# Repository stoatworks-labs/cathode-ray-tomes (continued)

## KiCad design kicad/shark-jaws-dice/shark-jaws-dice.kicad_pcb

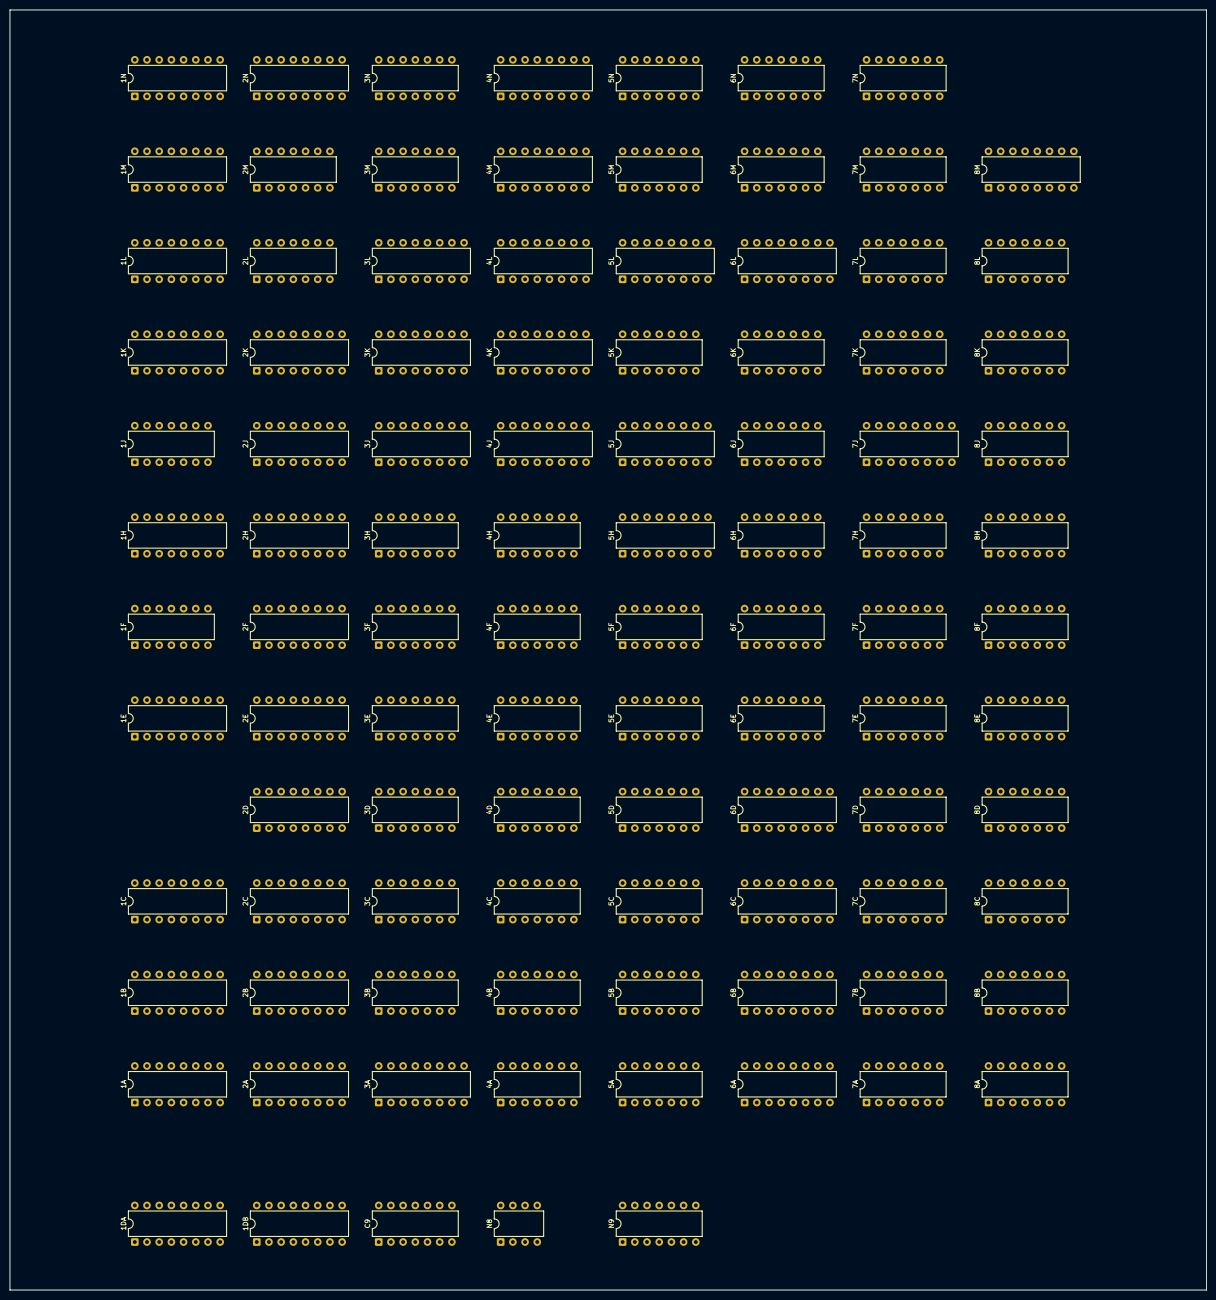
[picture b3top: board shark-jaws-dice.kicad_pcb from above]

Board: 2 copper layers, 249.2 x 266.6 mm, 99 parts (0 on the bottom side), 315 nets, no tracks yet.

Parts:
1A, 1B, 1H, 1K, 3A, 6D: 9322; DIP-16_W7.62mm
1C, 3L, 8M: 9314; DIP-16_W7.62mm
1DA, 1DB: 74S287; DIP-16_W7.62mm
1E: 74174; DIP-16_W7.62mm
1F, 7L: 7486; DIP-14_W7.62mm
1J, 5B: 7430; DIP-14_W7.62mm
1L, 1M, 1N, 2J, 2K, 2N, 4J, 4K, 4M, 4N, 5H, 5J: 9316; DIP-16_W7.62mm
2A, 2B, 2C, 2D, 2E, 2F, 2H: 74165; DIP-16_W7.62mm
2L, 4B, 8B, 8F, 8J: 7404; DIP-14_W7.62mm
2M, 4A, 5K, 7N, 8K: 7400; DIP-14_W7.62mm
3B: 74164; DIP-14_W7.62mm
3C, 3E, 5M, 5N, 7E, 8A, 8L: 7402; DIP-14_W7.62mm
3D, 3M, 7D, 7H: 7408; DIP-14_W7.62mm
3F, 4E, 5A, 6H, 6M, 6N, 7C, 7F, 7K, 7M, 8C, 8D, 8E: 7474; DIP-14_W7.62mm
3H, 4C: 7420; DIP-14_W7.62mm
3J, 3K, 4L: 7485; DIP-16_W7.62mm
3N, 4D, 6K: 74107; DIP-14_W7.62mm
4F, 6J, 7B, 8H: 7410; DIP-14_W7.62mm
4H: 7427; DIP-14_W7.62mm
5C, 5D, 5E, 5F, 7A: 7493; DIP-14_W7.62mm
5L, 6L: 74153; DIP-16_W7.62mm
6A, 6B: 9312; DIP-16_W7.62mm
6C: 7448; DIP-16_W7.62mm
6E, 6F: 7490; DIP-14_W7.62mm
7J: 9310; DIP-16_W7.62mm
C9: 556; DIP-14_W7.62mm
N8: 555; DIP-8_W7.62mm
N9: 556; DIP-14_W7.62mm

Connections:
1A-1: 1A.1, 1B.1, 3A.1, 6L.9
1A-4: 1A.4, 2D.6, 2E.6, 2F.6, 2H.6
1A-7: 1A.7, 2D.5, 2E.5, 2F.5, 2H.5
1A-9: 1A.9, 2D.3, 2E.3, 2F.3, 2H.3
1A-12: 1A.12, 2D.4, 2E.4, 2F.4, 2H.4
1B-4: 1B.4, 2D.14, 2E.14, 2F.14, 2H.14
1B-7: 1B.7, 2D.13, 2E.13, 2F.13, 2H.13
1B-9: 1B.9, 2D.11, 2E.11, 2F.11, 2H.11
1B-12: 1B.12, 2D.12, 2E.12, 2F.12, 2H.12
1C-1: 1C.1, 4A.8
1DA-1: 1DA.1, 1DB.1
1DA-2: 1DA.2, 1DB.2
1DA-5: 1DA.5, 1DB.5
1DA-13: 1DA.13, 3E.1
1DB-15: 1DB.15, N9.9
1E-13: 1E.13, 1F.11
1E-14: 1E.14, 7E.10
1F-4: 1F.4, 1H.12
1F-5: 1F.5, 1F.10, 4H.6
1F-9: 1F.9, 1H.7
1F-12: 1F.12, 3D.3
1F-13: 1F.13, 7K.5
1H-3: 1H.3, 1K.4
1H-6: 1H.6, 1K.7
1H-10: 1H.10, 1K.9
1H-13: 1H.13, 1K.12
1J-3: 1J.3, 2L.10
1J-4: 1J.4, 2L.8
1J-8: 1J.8, 6H.10
1L-3: 1L.3, 8L.2, 8M.13
1L-4: 1L.4, 7L.6
1L-9: 1L.9, 1M.9, 2M.6
1L-11: 1L.11, 3M.9
1L-15: 1L.15, 1M.7, 2M.5
1M-15: 1M.15, 2M.4, 3M.10
1N-7: 1N.7, 2M.1, 2N.15
1N-9: 1N.9, 2M.3, 2N.9
2A-1: 2A.1, 3A.4, 7N.9
2A-3: 2A.3, 2B.3, 2C.3
2A-4: 2A.4, 2B.4, 2C.4
2A-5: 2A.5, 2B.5, 2C.5
2A-6: 2A.6, 2B.6, 2C.6
2A-9: 2A.9, 2B.10
2A-11: 2A.11, 2B.11, 2C.11
2A-12: 2A.12, 2B.12, 2C.12
2A-13: 2A.13, 2B.13, 2C.13
2A-14: 2A.14, 2B.14, 2C.14
2A-15: 2A.15, 2B.15, 2C.15, 3C.8, 7K.8
2B-9: 2B.9, 2C.10
2C-1: 2C.1, 3A.7, 7N.10
2C-7: 2C.7, 3C.9
2D-1: 2D.1, 3B.13
2D-7: 2D.7, 3C.12
2D-15: 2D.15, 3C.11, 3H.8
2E-1: 2E.1, 3A.9
2E-2: 2E.2, 2F.2, 2H.2, 3F.5
2E-7: 2E.7, 3E.9
2E-10: 2E.10, 2F.9
2E-15: 2E.15, 2F.15, 2H.15, 3E.8, 3F.8
2F-10: 2F.10, 2H.9
2H-1: 2H.1, 3A.12
2J-7: 2J.7, 2K.15, 3M.5
2J-9: 2J.9, 2K.9, 2M.8
2J-15: 2J.15, 3M.4
2K-3: 2K.3, 2L.4, 2M.13
2K-4: 2K.4, 2M.11
2L-3: 2L.3, 3L.12
2L-5: 2L.5, 3H.6
2L-6: 2L.6, 3M.13
2L-12: 2L.12, 3H.5
2M-10: 2M.10, 3M.6, 3N.9
2M-12: 2M.12, 3L.10
2N-4: 2N.4, 8L.4
3C-1: 3C.1, 3D.13
3C-4: 3C.4, 3D.10
3D-2: 3D.2, 3E.4
3F-2: 3F.2, 3F.6
3F-4: 3F.4, 3F.9
3J-2: 3J.2, 3K.7
3J-3: 3J.3, 3K.6
3J-7: 3J.7, 3L.7
3L-1: 3L.1, 5K.6
3L-3: 3L.3, 4L.7
3L-15: 3L.15, 5N.2, 8J.13
3M-1: 3M.1, 8K.3
3M-2: 3M.2, 8J.9, 8K.6
3M-3: 3M.3, 5H.4
3N-12: 3N.12, 4F.4, 4M.15
4A-3: 4A.3, 4A.4, 7L.10
4A-5: 4A.5, 4B.10
4A-11: 4A.11, 7D.5
4A-12: 4A.12, 4H.8
4A-13: 4A.13, 4B.12
4B-9: 4B.9, C9.9
4C-6: 4C.6, 7C.13
4C-8: 4C.8, 7D.4
4E-3: 4E.3, 8F.12
4E-5: 4E.5, 5A.11, 5D.14
4E-12: 4E.12, 4F.12
4F-3: 4F.3, 4M.7, 4N.15
4F-6: 4F.6, 4M.9, 4N.9
4F-8: 4F.8, 7E.5
4F-9: 4F.9, 7E.1
4H-3: 4H.3, 6K.3
4H-4: 4H.4, 8J.6
4H-12: 4H.12, 4J.4
4J-3: 4J.3, 6J.6
4J-9: 4J.9, 4K.9, 5K.8
4J-15: 4J.15, 4K.7, 5K.10
4N-3: 4N.3, 5N.3, 5N.4
4N-4: 4N.4, 5N.1
5A-12: 5A.12, 5B.8
5H-5: 5H.5, 8J.8
5H-9: 5H.9, 5J.9, 5K.11
5H-15: 5H.15, 5J.10
5J-15: 5J.15, 5K.13, 6K.9
5K-3: 5K.3, 5L.1
5N-6: 5N.6, 6N.5
6A-1: 6A.1, 6C.15
6A-4: 6A.4, 6C.12
6A-5: 6A.5, 6C.9
6A-9: 6A.9, 6C.11
6A-15: 6A.15, 7E.9
6B-1: 6B.1, 6C.13
6B-4: 6B.4, 6C.14
6B-9: 6B.9, 6C.10
6B-15: 6B.15, 7E.8
6C-1: 6C.1, 6D.7
6C-2: 6C.2, 6D.12
6C-6: 6C.6, 6D.9
6C-7: 6C.7, 6D.4
6D-2: 6D.2, 6F.1, 6F.12
6D-3: 6D.3, 6E.1, 6E.12
6D-5: 6D.5, 6F.9
6D-6: 6D.6, 6E.9
6D-10: 6D.10, 6E.11
6D-11: 6D.11, 6E.14, 6F.11
6D-13: 6D.13, 6E.8
6D-14: 6D.14, 6F.8
6F-14: 6F.14, 7D.3
6H-2: 6H.2, 7J.11, 8L.8
6H-5: 6H.5, 6J.10
6J-2: 6J.2, 7H.6, 8H.3
6J-3: 6J.3, 7L.11
6J-8: 6J.8, 7J.1
6J-12: 6J.12, 7H.2
6L-7: 6L.7, 7K.3
6L-10: 6L.10, 6M.6
6L-11: 6L.11, 6M.9
6N-1: 6N.1, 7N.6
6N-8: 6N.8, 6N.12
7A-1: 7A.1, 7A.12
7A-11: 7A.11, 8A.12
7B-4: 7B.4, 7B.5
7B-6: 7B.6, 8E.2
7B-12: 7B.12, 7C.1
7C-3: 7C.3, 7D.11
7D-6: 7D.6, 7E.6
7E-11: 7E.11, 8C.1, 8C.12, 8C.13
7E-13: 7E.13, 8E.4
7F-1: 7F.1, 7H.3
7F-13: 7F.13, 7H.11
7H-1: 7H.1, 8H.6
7H-8: 7H.8, 8H.10, 8H.13
7H-12: 7H.12, 8H.12
7H-13: 7H.13, 8H.8
7J-7: 7J.7, 8J.4
7J-12: 7J.12, 8L.9
7J-15: 7J.15, 8J.3
7L-1: 7L.1, 8M.15
7L-2: 7L.2, 7M.5
7L-3: 7L.3, 8J.1, 8L.5
7L-4: 7L.4, 8L.1
7L-5: 7L.5, 7M.9
7L-8: 7L.8, 8L.11, 8L.12
7M-3: 7M.3, 7N.3
7M-11: 7M.11, 7N.11
7N-4: 7N.4, 7N.5, N8.3
8A-9: 8A.9, 8A.13
8A-10: 8A.10, 8A.11
8C-2: 8C.2, 8C.9
8C-6: 8C.6, 8D.1, 8D.13
8D-5: 8D.5, 8D.12
8E-11: 8E.11, 8F.10
8F-6: 8F.6, 8H.9
8K-11: 8K.11, C9.6
8L-3: 8L.3, 8M.12
+5V: 1A.16, 1B.16, 1E.16, 1F.14, 1H.16, 1J.14, 1K.16, 1L.16, 1M.16, 1N.16, 2A.16, 2B.16, 2C.16, 2D.16, 2E.16, 2F.16, 2H.16, 2J.16, 2K.16, 2L.14, 2M.14, 2N.16, 3A.16, 3B.14, 3C.14, 3D.14, 3E.14, 3F.14, 3H.14, 3J.16, 3K.16, 3M.14, 3N.14, 4A.14, 4B.14, 4C.14, 4D.14, 4E.14, 4F.14, 4H.14, 4J.16, 4K.16, 4L.16, 4M.16, 4N.16, 5A.14, 5B.14, 5C.5, 5D.5, 5E.5, 5F.5, 5H.16, 5J.16, 5K.14, 5L.16, 5M.14, 5N.14, 6A.16, 6B.16, 6C.16, 6D.16, 6E.5, 6F.5, 6H.14, 6J.14, 6K.14, 6L.16, 6M.14, 6N.14, 7A.5, 7B.14, 7C.14, 7D.14, 7E.14, 7F.14, 7H.14, 7J.16, 7K.14, 7L.14, 7M.14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
GND: 1A.8, 1A.15, 1B.8, 1B.15, 1C.2, 1C.5, 1C.11, 1C.14, 1E.8, 1F.7, 1H.8, 1H.15, 1J.7, 1K.8, 1K.15, 1L.8, 1M.6, 1M.8, 1N.4, 1N.5, 1N.6, 1N.8, 2A.8, 2A.10, 2B.8, 2C.8, 2D.8, 2D.10, 2E.8, 2F.8, 2H.8, 2H.10, 2J.8, 2K.5, 2K.8, 2L.7, 2M.7, 2N.8, 3A.8, 3A.15, 3B.7, 3C.7, 3D.7, 3E.7, 3F.7, 3H.7, 3J.8, 3K.8, 3L.2, 3L.5, 3L.11, 3L.14, 3M.7, 3N.7, 4A.7, 4B.7, 4C.7, 4D.7, 4E.7, 4F.7, 4H.7, 4J.8, 4K.4, 4K.5, 4K.6, 4K.8, 4L.8, 4M.5, 4M.6, 4M.8, 4N.5, 4N.8, 5A.7, 5B.7, 5C.10, 5D.10, 5E.10, 5F.10, 5H.3, 5H.8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
VCC: 1C.9, 1E.1, 1L.1, 1L.5, 1L.6, 1L.7, 1M.1, 1M.3, 1M.4, 1M.5, 1M.10, 1N.1, 1N.3, 1N.10, 2J.1, 2J.3, 2J.4, 2J.5, 2J.6, 2J.10, 2K.1, 2K.6, 2K.7, 2K.10, 2N.1, 2N.5, 2N.6, 2N.7, 2N.10, 3B.1, 3B.2, 3F.1, 3F.10, 3J.4, 3K.2, 3K.3, 3K.4, 3K.9, 3K.10, 3K.11, 3K.12, 3L.9, 3N.1, 3N.4, 3N.8, 3N.10, 3N.11, 3N.13, 4D.1, 4D.4, 4D.8, 4D.11, 4E.1, 4E.4, 4E.10, 4E.13, 4J.1, 4J.5, 4J.6, 4J.7, 4J.10, 4K.3, 4K.10, 4L.3, 4L.4, 4M.1, 4M.3, 4M.4, 4M.10, 4N.1, 4N.6, 4N.7, 4N.10, 5A.2, 5A.4, 5A.10, 5A.13, 5B.1, 5B.2, 5B.12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
_1H: 4B.3, 4J.2, 4K.2, 5D.1, 5D.12, 8M.4
_1Hn: 1E.9, 1N.2, 2N.2, 4B.4
_1V: 4F.1, 5F.1, 5F.12
_2H: 4A.10, 5B.4, 5D.9, 6A.11, 8M.6
_2V: 5F.9, 6B.11
_4H: 1E.6, 4B.1, 5B.5, 5D.8, 6A.12
_4Hn: 3B.8, 4A.9, 4B.2
_4V: 4B.11, 4F.2, 5F.8, 6B.12
_8H: 1E.4, 3E.6, 5C.14, 5D.11, 6A.10, 6B.10
_8V: 5E.14, 5F.11, 6A.13, 6B.13
_16H: 1E.3, 3E.5, 4B.13, 4C.13, 5A.3, 5C.1, 5C.12, 7D.13
_16V: 4C.2, 4F.11, 5E.1, 5E.12
_32H: 4C.9, 4H.11, 5C.9, 7B.2
_32V: 4C.1, 4F.10, 5E.9, 7C.11
_64H: 4C.10, 4H.10, 5B.6, 5C.8, 7D.12
_64V: 4C.4, 5E.8, 7E.3, 8C.3, 8C.11
_128H: 4C.12, 4D.12, 4H.9, 5B.3, 5C.11, 7B.1
_128V: 4C.5, 4D.9, 5E.11, 7E.2, 8F.5, 8H.2
_256H: 4D.3, 5B.11, 7B.13, 8H.5
_256Hn: 4D.2, 6D.1, 6J.13
_256V: 4D.5, 4F.13, 6K.12, 8E.3
_AH3: 1J.1, 4J.12
_AH4: 2L.9, 4J.11
_AHWIN: 4K.15, 5K.9, 7K.11
_ATTRACT: 7B.3, 8D.3, 8D.11, 8E.9
_ATTRACTn: 6M.2, 7D.1, 7F.2, 7F.12, 8E.8
_AV1: 1H.11, 1J.6, 5H.14
_AV2: 1H.14, 1J.2, 5H.13
_AV3: 1H.5, 1J.5, 5H.12
_AV4: 1H.2, 2L.11, 3K.13, 5H.11
_AVWIN: 5L.7, 7K.12
_BV1: 1K.11, 2K.14
_BV2: 1K.14, 2K.13
_BV3: 1K.5, 2K.12
_BV4: 1K.2, 2K.11, 3K.14
_BV5: 3D.1, 4N.12
_CATCH: 6H.12, 8J.5, 8L.10
_CH3: 2N.12, 3H.13
_CH4: 2N.11, 3H.12
_CHWIN: 1N.15, 2M.2, 3H.10
_CLOCKn: 2A.2, 2B.2, 2C.2, 2D.2, 3F.3, 4E.2, 4E.6, 4M.2, 4N.2, 8M.3
_COMPBLANK: 1J.12, 8K.8
_CREDITn: 7E.12, 8D.9
_CV1: 1K.10, 1L.10, 6N.9
_CV2: 1K.13, 1L.14
_CV3: 1K.6, 1L.13
_CV4: 1K.3, 1L.12
_CVWIN: 3E.3, 3H.9, 3M.8
_D1: 1A.3, 1B.11, 1C.3, 1DA.12
_D2: 1A.6, 1B.14, 1C.4, 1DA.11
_D3: 1A.13, 1B.5, 1C.6, 1DA.10
_D4: 1A.10, 1B.2, 1C.7, 1DA.9
_D5: 1A.11, 1B.3, 1C.15
_D6: 1A.14, 1B.6, 1C.13
_D7: 1A.5, 1B.13, 1C.12
_D8: 1A.2, 1B.10, 1C.10
_DIVERENABLEn: 1DB.14, 5N.10
_ENDGAMEn: 8F.11, N9.5
_FISHSCORE: 3C.2, 7D.2, C9.5
_HALFSEC: 6H.3, 6H.11, 6M.11, 7A.14, 7J.2, 7K.1, 7M.1, 7M.13, 8B.8, 8M.1
_HALFSECn: 4B.8, 5K.4, 8B.9
_HBLANK: 7C.6, 7H.5, 7N.1
_HBLANKn: 3D.4, 7C.5, 8K.9
_HRESET: 4E.11, 5A.8, 5C.2, 5C.3, 5D.2, 5D.3, 5F.14
_HRESETn: 3B.9, 3F.13, 4D.13, 5A.1, 5A.9
_HSYNC: 2J.2, 2K.2, 5A.6, 5H.2, 5J.2, 6N.3, 7L.9
_HSYNC1: 1L.2, 1M.2, 3C.3, 3C.5, 4B.6, 6N.11
_HSYNCn: 4B.5, 5A.5
_JOYDOWN: 8H.1, 8K.1
_JOYLEFT: 6J.1, 7L.13, 8J.11
_JOYRIGHT: 6M.3, 7L.12, 8H.4
_JOYUP: 8H.11, 8K.5
_LD1An: 3A.3, 3A.5, 3B.3
_LD1Bn: 2B.1, 3B.4
_LD1Cn: 1H.1, 3A.2, 3A.6, 3B.5, 4H.5, 6L.14
_LD2An: 3A.11, 3A.13, 3B.10
_LD2Bn: 2F.1, 3B.11
_LD2Cn: 1K.1, 3A.10, 3A.14, 3B.12, 6L.2
_LH1: 4L.9, 4M.13
_LH2: 4L.11, 4M.12
_LH3: 4L.14, 4M.11, 7K.2
_LH4: 3N.3, 4F.5, 4L.1
_LHWIN: 3F.11, 3N.2
_LRGFISH: 3D.5, 3E.10, 6J.11
_LRGFISHDIR: 6M.12, 8J.12
_LV0: 2J.14, 2L.13, 3K.1
_LV1: 2J.13, 3H.4, 3J.9
_LV2: 2J.12, 3H.2, 3J.11
_LV3: 2J.11, 3H.1, 3J.14
_LV4: 2M.9, 3J.1, 3M.12, 3N.5
_LVWIN: 3E.2, 3F.12, 3M.11
_MEDFISH: 1J.11, 3C.10, 3D.9, 6J.9, 7H.4, 7H.10, 8K.12
_MH1: 4K.14, 4L.10
_MH2: 4K.13, 4L.12
_MH3: 4K.12, 4L.13, 7K.13
_MH4: 4K.11, 4L.15
_MV1: 3K.15, 5J.14, 5L.2
_MV2: 3J.10, 5J.13, 5L.14
_MV3: 3J.12, 5J.12, 5K.1
_MV4: 3J.13, 5J.11, 5K.2
_MV5: 3J.15, 5K.12, 6K.5
_Q: 8D.10, 8E.10, 8F.8
_RESET: 3C.6, 6H.9
_RESETn: 4K.1, 5J.1, 6H.8
_SCOREWIN: 6C.4, 7E.4
_SCOREn: 1E.15, 2L.1
_SHARKENABLEn: 1DA.14, 5N.8, 5N.9, 7N.8
_SMLFISH: 3C.13, 3D.12, 7N.2, 7N.13, 8K.13
_SMLFISHDIR: 6L.13, 8J.2
_START: 6E.2, 6E.3, 6F.2, 6F.3, 7A.2, 7A.3, 8A.8, 8E.6
_STARTn: 8E.5, 8E.13, N8.2, N9.6
_STOPH: 4H.13, 7F.6
_STOPHn: 6J.4, 7F.5
_STOPVn: 7F.9, 8K.2, 8K.4
_SWLEFTn: 4H.1, 6M.1, 8J.10
_V1: 1DA.6, 1DB.6, 1H.9
_V2: 1DA.7, 1DB.7, 1F.6
_V3: 1DA.4, 1DB.4, 1F.8
_V4: 1DA.3, 1DB.3, 1H.4
_VAEQB: 3J.6, 3L.6, 6L.3, 6L.4, 6L.5
_VBLANK: 7C.8, 7H.9, 7N.12
_VBLANKn: 7C.9, 8K.10
_VRESET: 4E.8, 5E.2, 5E.3, 5F.2, 5F.3, 5K.5, 5N.5, 6J.5, 6N.2
_VRESETn: 2N.3, 4A.2, 4D.10, 4E.9, 4H.2, 7F.3, 7F.11, 8L.6
_VSYNCn: 4A.1, 4A.6

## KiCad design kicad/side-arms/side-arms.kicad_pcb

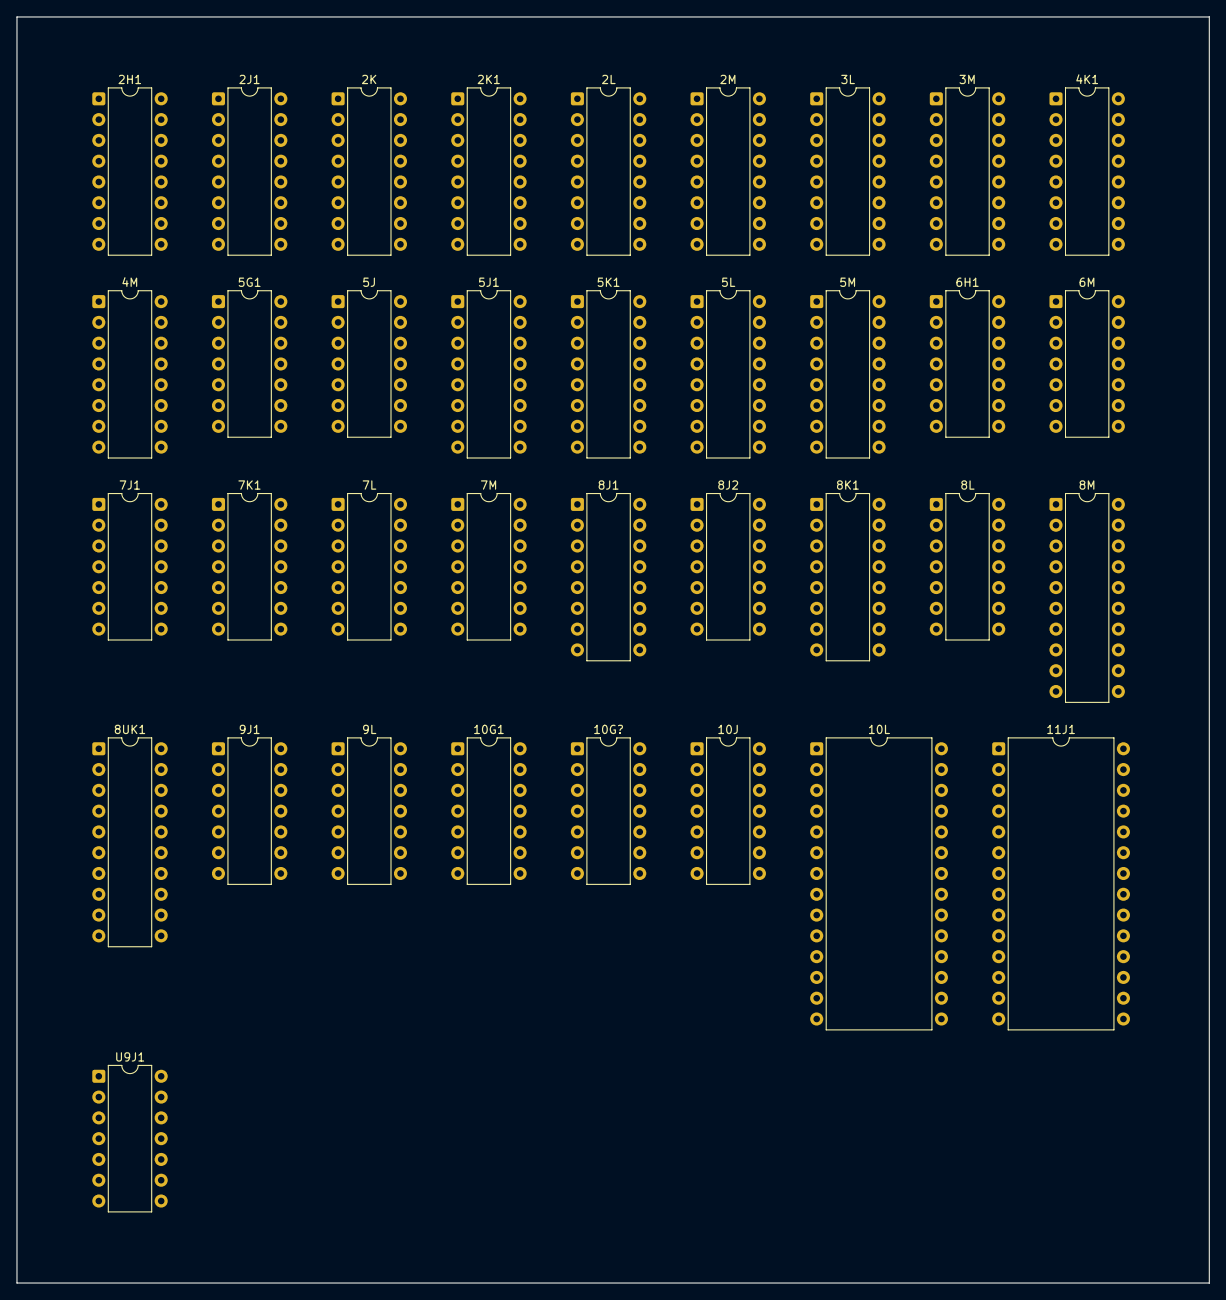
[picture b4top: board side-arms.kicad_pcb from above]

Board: 2 copper layers, 145.7 x 154.7 mm, 36 parts (0 on the bottom side), 149 nets, no tracks yet.

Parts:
2H1, 2J1, 2K, 2K1, 2L, 2M, 5K1, 5M: 74LS283; DIP-16_W7.62mm
3L, 3M, 4K1, 4M, 5J1, 5L, 8J1, 8K1: 74LS191; DIP-16_W7.62mm
5G1, 5J: 74LS08; DIP-14_W7.62mm
6H1, 6M, 8J2, 8L: 74LS30; DIP-14_W7.62mm
7J1, 7L: 74LS74; DIP-14_W7.62mm
7K1, 7M, 10G1, 10G?, 10J: 74LS86; DIP-14_W7.62mm
8M, 8UK1: 74LS374; DIP-20_W7.62mm
9J1, 9L: 74LS00; DIP-14_W7.62mm
10L: 74LS00; DIP-28_W15.24mm
11J1: 27128; DIP-28_W15.24mm
U9J1: 74LS00; DIP-14_W7.62mm

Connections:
/D~U: 4K1.5, 5J1.5, 8J1.5, 8K1.5, 10G1.3
/H6: 2J1.3, 10G1.13
/HS0: 2K1.4, 6H1.12, 10G1.10
/HS1: 2K1.1, 6H1.11, 7K1.13
/HS2: 2K1.13, 6H1.6, 7K1.10, 9J1.2
/HS3: 2K1.10, 6H1.5, 7K1.5
/HS4: 2J1.4, 6H1.4, 7K1.2
/HS5: 2J1.1, 11J1.10
/HS6: 2J1.13, 11J1.9
/HS7: 2J1.10, 11J1.8
/HS8: 10G1.6, 11J1.7
/HSC: 2J1.9, 10G1.5
/HSCAN: 8J1.14, 8K1.14
/O3: 7K1.1, 8UK1.9
/O4: 7K1.4, 8UK1.12
/O5: 7K1.9, 8UK1.15
/O6: 7K1.12, 8UK1.16
/O7: 8UK1.19, 10G1.9
/RCO: 4K1.13, 5J1.4
/Rc: 8J1.4, 8K1.13
/S0: 5K1.4, 11J1.6
/S1: 5K1.1, 9J1.1, 11J1.5
/S2: 5K1.13, 10G1.12, 11J1.4
/S3: 5K1.10, 11J1.3
/S4: 2H1.10, 11J1.25
/S5: 2H1.13, 11J1.24
/S6: 2H1.1, 11J1.21
/S7: 2H1.4, 11J1.23
/STARON: 4K1.11, 5J1.11, 8J1.11, 8K1.11
/VSCAN: 4K1.14, 5J1.14
/sarms/D~U: 3L.5, 3M.5, 4M.5, 5L.5, 10J.3
/sarms/H6: 2L.3, 10J.13
/sarms/HS0: 2M.4, 6M.12, 10J.10
/sarms/HS1: 2M.1, 7M.13
/sarms/HS2: 2M.13, 6M.6, 7M.10
/sarms/HS3: 2M.10, 6M.5, 7M.5
/sarms/HS4: 2L.4, 6M.4, 7M.2
/sarms/HS5: 2L.1, 10L.10
/sarms/HS6: 2L.13, 10L.9
/sarms/HS7: 2L.10, 10L.8
/sarms/HS8: 10J.6, 10L.7
/sarms/HSC: 2L.9, 10J.5
/sarms/HSCAN: 3L.14, 3M.14
/sarms/O0: 8M.19, 10J.9
/sarms/O1: 7M.12, 8M.16
/sarms/O2: 7M.9, 8M.15
/sarms/O3: 7M.4, 8M.12
/sarms/O4: 7M.1, 8M.9
/sarms/RCO: 4M.13, 5L.4
/sarms/Rc: 3L.4, 3M.13
/sarms/S0: 5M.4, 10L.6
/sarms/S1: 5M.1, 10L.5
/sarms/S2: 5M.13, 10J.12, 10L.4
/sarms/S4: 2K.4, 10L.25
/sarms/S5: 2K.1, 10L.24
/sarms/S6: 2K.13, 10L.21
/sarms/S7: 2K.10, 10L.23
/sarms/STARON: 3L.11, 3M.11, 4M.11, 5L.11
/sarms/VSCAN: 4M.14, 5L.14
/sarms/~C4: 2L.7, 2M.9
/sarms/~LD: 7L.1, 8L.4
/~C4: 2J1.7, 2K1.9
/~LD: 7J1.1, 8J2.4
GND: 2K1.7, 2M.7, 3L.1, 3L.9, 3L.10, 3L.15, 3M.1, 3M.4, 3M.9, 3M.10, 3M.15, 4K1.1, 4K1.4, 4K1.9, 4K1.10, 4K1.15, 4M.1, 4M.4, 4M.9, 4M.10, 4M.15, 5J1.1, 5J1.9, 5J1.10, 5J1.15, 5K1.7, 5L.1, 5L.9, 5L.10, 5L.15, 5M.7, 8J1.1, 8J1.9, 8J1.10, 8J1.15, 8K1.1, 8K1.4, 8K1.9, 8K1.10, 8K1.15, 8M.1, 8UK1.1, 10G1.1, 10J.1, 10L.14, 10L.20, 10L.22, 11J1.14, 11J1.20, 11J1.22
unnamed: 2H1.6, 5J1.3
unnamed: 2H1.2, 5J1.2
unnamed: 2H1.15, 5J1.6
unnamed: 2H1.11, 5J1.7
unnamed: 2H1.7, 5K1.9
unnamed: 2J1.6, 8J1.3
unnamed: 2J1.2, 8J1.2
unnamed: 2J1.15, 8J1.6
unnamed: 2J1.11, 8J1.7
unnamed: 2K1.6, 8K1.3
unnamed: 2K1.2, 8K1.2
unnamed: 2K1.15, 8K1.6
unnamed: 2K1.11, 8K1.7
unnamed: 2K.6, 5L.3
unnamed: 2K.2, 5L.2
unnamed: 2K.15, 5L.6
unnamed: 2K.11, 5L.7
unnamed: 2K.7, 5M.9
unnamed: 2L.6, 3L.3
unnamed: 2L.2, 3L.2
unnamed: 2L.15, 3L.6
unnamed: 2L.11, 3L.7
unnamed: 2M.6, 3M.3
unnamed: 2M.2, 3M.2
unnamed: 2M.15, 3M.6
unnamed: 2M.11, 3M.7
unnamed: 3L.13, 7L.3
unnamed: 4K1.3, 5K1.6
unnamed: 4K1.2, 5K1.2
unnamed: 4K1.6, 5K1.15
unnamed: 4K1.7, 5K1.11
unnamed: 4M.3, 5M.6
unnamed: 4M.2, 5M.2
unnamed: 4M.6, 5M.15
unnamed: 4M.7, 5M.11
unnamed: 5G1.2, 9J1.3
unnamed: 5G1.3, 8J2.12
unnamed: 5G1.5, 5G1.9, 5G1.12, 9J1.8
unnamed: 5J.3, 8L.12
unnamed: 5J.5, 5J.9, 5J.12, 9L.8
unnamed: 7J1.3, 8J1.13
unnamed: 7J1.2, 7J1.6, 10G1.4
unnamed: 7K1.3, 8J2.1
unnamed: 7K1.6, 8J2.3
unnamed: 7K1.8, 8J2.5
unnamed: 7K1.11, 8J2.11
unnamed: 7L.2, 7L.6, 10J.4
unnamed: 7M.3, 8L.1
unnamed: 7M.6, 8L.3
unnamed: 7M.8, 8L.5
unnamed: 7M.11, 8L.11
unnamed: 8J2.6, U9J1.6
unnamed: 8J2.8, 9J1.9, 9J1.10
unnamed: 8L.6, 9L.6
unnamed: 8L.8, 9L.9, 9L.10
unnamed: 6M.8, 8M.11
unnamed: 5J.4, 8M.2
unnamed: 5J.10, 8M.5
unnamed: 5J.13, 8M.6
unnamed: 6H1.8, 8UK1.11
unnamed: 5G1.4, 8UK1.2
unnamed: 5G1.10, 8UK1.5
unnamed: 5G1.13, 8UK1.6
unnamed: 10G1.8, U9J1.5
unnamed: 5G1.1, 10G1.11
unnamed: 9L.5, 10J.8
unnamed: 5J.1, 10J.11
unnamed: 8M.18, 10L.11
unnamed: 8M.17, 10L.12
unnamed: 8M.14, 10L.13
unnamed: 8M.13, 10L.15
unnamed: 8M.8, 10L.16
unnamed: 8M.7, 10L.17
unnamed: 8M.4, 10L.18
unnamed: 8M.3, 10L.19
unnamed: 5J.2, 10L.3
unnamed: 8UK1.18, 11J1.11
unnamed: 8UK1.17, 11J1.12
unnamed: 8UK1.14, 11J1.13
unnamed: 8UK1.13, 11J1.15
unnamed: 8UK1.8, 11J1.16
unnamed: 8UK1.7, 11J1.17
unnamed: 8UK1.4, 11J1.18
unnamed: 8UK1.3, 11J1.19
VCC: 6H1.1, 6H1.2, 6H1.3, 6M.1, 6M.2, 7J1.4, 7L.4, 8J2.2, 8L.2, 9L.4, 10L.1, 10L.2, 10L.26, 10L.27, 10L.28, 11J1.1, 11J1.2, 11J1.26, 11J1.27, 11J1.28, U9J1.4

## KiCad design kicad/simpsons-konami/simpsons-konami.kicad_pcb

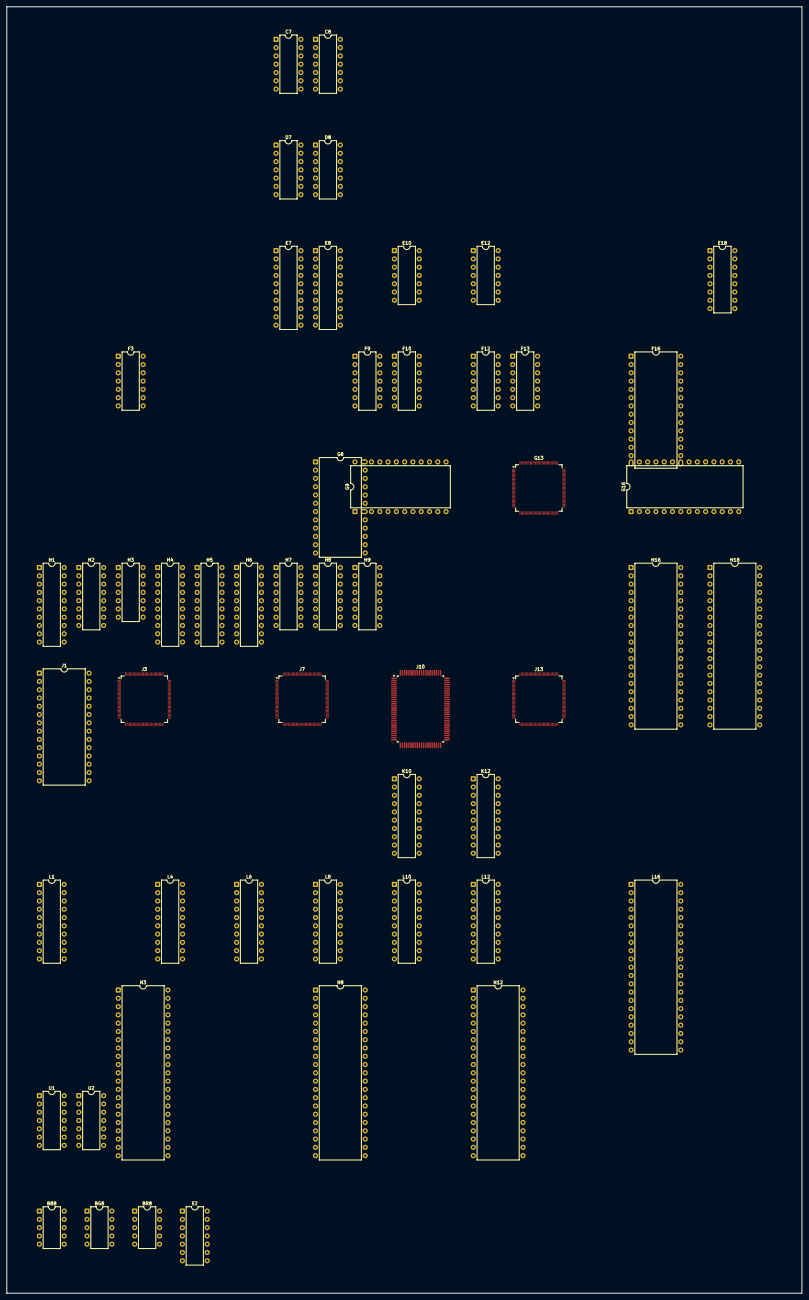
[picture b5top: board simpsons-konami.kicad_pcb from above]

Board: 2 copper layers, 243.9 x 394.6 mm, 53 parts (0 on the bottom side), 405 nets, no tracks yet.

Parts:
BB8: 052535; DIP-10_W7.62mm
BG8: 052535; DIP-10_W7.62mm
BR8: 052535; DIP-10_W7.62mm
C7, C8: 74LS07; DIP-14_W7.62mm
D7, D8: 74LS07; DIP-14_W7.62mm
E7, E8: 74LS273; DIP-20_W7.62mm
E10: 74LS08; DIP-14_W7.62mm
E12: 74LS164; DIP-14_W7.62mm
E18: 74LS367; DIP-16_W7.62mm
E?: 74LS04; DIP-14_W7.62mm
F3: 74LS04; DIP-14_W7.62mm
F9, F10, F12: 74LS32; DIP-14_W7.62mm
F13: 74LS74; DIP-14_W7.62mm
F16: MB8464A-10W-15W; DIP-28_W15.24mm
G8, G9: HM6116P-3; DIP-24_W15.24mm
G13: 052109; TQFP-120_14x14mm_P0.4mm
G16: MB8464A-10W-15W; DIP-28_W15.24mm
H1, H4, H5, H6: 74LS245; DIP-20_W7.62mm
H2: 74LS367; DIP-16_W7.62mm
H3: 74LS04; DIP-14_W7.62mm
H7, H8, H9: 74LS157; DIP-16_W7.62mm
H16, H18: 955D05-06-07-08; DIP-40_W15.24mm
J1: MB8464A-10W-15W; DIP-28_W15.24mm
J3: 053246; TQFP-120_14x14mm_P0.4mm
J7: 053247; TQFP-120_14x14mm_P0.4mm
J10: 053251; PQFP-100_14x20mm_P0.65mm
J13: 051962; TQFP-120_14x14mm_P0.4mm
K10, K12: 74LS374; DIP-20_W7.62mm
L1, L4, L6, L8, L10, L12: 74LS374; DIP-20_W7.62mm
L16: 065A08; DIP-42_W15.24mm
N3, N8, N12: 065A08; DIP-42_W15.24mm
U1: 74LS32; DIP-14_W7.62mm
U2: 74LS04; DIP-14_W7.62mm

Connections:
/ACOL0: J10.57, J13.46
/ACOL1: J10.58, J13.47
/ACOL2: J10.59, J13.48
/ACOL3: J10.60, J13.49
/APAL0: J10.61, J13.51
/APAL1: J10.62, J13.52
/APAL2: J10.63, J13.53
/BCOL0: J10.66, J13.30
/BCOL1: J10.67, J13.32
/BCOL2: J10.68, J13.33
/BCOL3: J10.69, J13.34
/BPAL0: J10.70, J13.36
/BPAL1: J10.71, J13.37
/BPAL2: J10.72, J13.38
/COLO~CS: F9.10, F10.1
/CRAM~CS: H5.19, H6.19, H7.1, H8.1, H9.1
/DB0: G13.56, H4.2, H5.2, H6.2, J7.30, J10.80, J13.79
/DB1: G13.57, H4.3, H5.3, H6.3, J7.29, J10.79, J13.80
/DB2: G13.58, H4.4, H5.4, H6.4, J7.28, J10.77, J13.81
/DB3: G13.59, H4.5, H5.5, H6.5, J7.27, J10.76, J13.82
/DB4: G13.60, H4.6, H5.6, H6.6, J7.26, J10.75, J13.83
/DB5: G13.62, H4.7, H5.7, H6.7, J7.25, J10.74, J13.84
/DB6: G13.63, H4.8, H5.8, H6.8, J7.24
/DB7: G13.64, H4.9, H5.9, H6.9, J7.23, J13.86
/FCOL0: J10.47, J13.59
/FCOL1: J10.48, J13.60
/FCOL2: J10.49, J13.62
/FCOL3: J10.50, J13.63
/FPAL0: J10.51, J13.65
/FPAL1: J10.52, J13.66
/FPAL3: J10.54, J13.67
/M~RD: G13.85, H2.14, H4.1, H5.1, H6.1, H8.14, J13.87
/OBJCLK6: E7.11, E8.11, E?.13, J3.12, J7.12, J10.41, J13.78
/OBJCLK12: J3.10, J7.10, J13.95
/OBJROMA0: J3.68, L16.10, N3.10, N8.10, N12.10
/OBJROMA1: J3.69, L16.9, N3.9, N8.9, N12.9
/OBJROMA2: J3.70, L16.8, N3.8, N8.8, N12.8
/OBJROMA3: J3.72, L16.7, N3.7, N8.7, N12.7
/OBJROMA4: J3.73, L16.6, N3.6, N8.6, N12.6
/OBJROMA5: J3.74, L16.5, N3.5, N8.5, N12.5
/OBJROMA6: J3.75, L16.4, N3.4, N8.4, N12.4
/OBJROMA7: J3.77, L16.3, N3.3, N8.3, N12.3
/OBJROMA8: J3.78, L16.41, N3.41, N8.41, N12.41
/OBJROMA9: J3.79, L16.40, N3.40, N8.40, N12.40
/OBJROMA10: J3.80, L16.39, N3.39, N8.39, N12.39
/OBJROMA11: J3.82, L16.38, N3.38, N8.38, N12.38
/OBJROMA12: J3.83, L16.37, N3.37, N8.37, N12.37
/OBJROMA13: J3.84, L16.36, N3.36, N8.36, N12.36
/OBJROMA14: J3.85, L16.35, N3.35, N8.35, N12.35
/OBJROMA15: J3.86, L16.34, N3.34, N8.34, N12.34
/OBJROMA16: J3.87, L16.33, N3.33, N8.33, N12.33
/OBJROMA17: J3.88, L16.2, N3.2, N8.2, N12.2
/OBJROMA18: J3.89, L16.1, N3.1, N8.1, N12.1
/OBJROMA19: J3.90, L16.42, N3.42, N8.42, N12.42
/OCOL0: J7.32, J10.30
/OCOL1: J7.33, J10.31
/OCOL2: J7.34, J10.32
/OCOL3: J7.35, J10.33
/PAL0: J7.36, J10.34
/PAL1: J7.37, J10.35
/PAL2: J7.38, J10.36
/PAL3: J7.39, J10.37
/PAL4: J7.40, J10.38
/PRI0: J7.42, J10.23
/PRI1: J7.43, J10.24
/PRI2: J7.44, J10.25
/PRI3: J7.45, J10.27
/PRI4: J7.47, J10.29
/RM~RD: G13.97, J13.96
/SCR_PQ: E18.10, G13.89
/SHD0: J7.48, J10.95
/SHD1: J7.49, J10.96
/XOBJROMD0: L1.3, N3.14
/XOBJROMD1: L1.4, N3.16
/XOBJROMD2: L1.7, N3.18
/XOBJROMD3: L1.8, N3.20
/XOBJROMD4: L1.13, N3.23
/XOBJROMD5: L1.14, N3.25
/XOBJROMD6: L1.17, N3.27
/XOBJROMD7: L1.18, N3.29
/XOBJROMD8: L4.3, N3.15
/XOBJROMD9: L4.4, N3.17
/XOBJROMD10: L4.7, N3.19
/XOBJROMD11: L4.8, N3.21
/XOBJROMD12: L4.13, N3.24
/XOBJROMD13: L4.14, N3.26
/XOBJROMD14: L4.17, N3.28
/XOBJROMD15: L4.18, N3.30
/XOBJROMD16: L6.3, N8.14
/XOBJROMD17: L6.4, N8.16
/XOBJROMD18: L6.7, N8.18
/XOBJROMD19: L6.8, N8.20
/XOBJROMD20: L6.13, N8.23
/XOBJROMD21: L6.14, N8.25
/XOBJROMD22: L6.17, N8.27
/XOBJROMD23: L6.18, N8.29
/XOBJROMD24: L8.3, N8.15
/XOBJROMD25: L8.4, N8.17
/XOBJROMD26: L8.7, N8.19
/XOBJROMD27: L8.8, N8.21
/XOBJROMD28: L8.13, N8.24
/XOBJROMD29: L8.14, N8.26
/XOBJROMD30: L8.17, N8.28
/XOBJROMD31: L8.18, N8.30
/YOBJROMD0: L10.3, N12.14
/YOBJROMD1: L10.4, N12.16
/YOBJROMD2: L10.7, N12.18
/YOBJROMD3: L10.8, N12.20
/YOBJROMD4: L10.13, N12.23
/YOBJROMD5: L10.14, N12.25
/YOBJROMD6: L10.17, N12.27
/YOBJROMD7: L10.18, N12.29
/YOBJROMD8: L12.3, N12.15
/YOBJROMD9: L12.4, N12.17
/YOBJROMD10: L12.7, N12.19
/YOBJROMD11: L12.8, N12.21
/YOBJROMD12: L12.13, N12.24
/YOBJROMD13: L12.14, N12.26
/YOBJROMD14: L12.17, N12.28
/YOBJROMD15: L12.18, N12.30
/YOBJROMD16: K10.3, L16.14
/YOBJROMD17: K10.4, L16.16
/YOBJROMD18: K10.7, L16.18
/YOBJROMD19: K10.8, L16.20
/YOBJROMD20: K10.13, L16.23
/YOBJROMD21: K10.14, L16.25
/YOBJROMD22: K10.17, L16.27
/YOBJROMD23: K10.18, L16.29
/YOBJROMD24: K12.3, L16.15
/YOBJROMD25: K12.4, L16.17
/YOBJROMD26: K12.7, L16.19
/YOBJROMD27: K12.8, L16.21
/YOBJROMD28: K12.13, L16.24
/YOBJROMD29: K12.14, L16.26
/YOBJROMD30: K12.17, L16.28
/YOBJROMD31: K12.18, L16.30
/colmix/A0: F10.2, H7.2, J10.85, U2.11
/colmix/COL0: H7.3, J10.19
/colmix/COL1: H7.6, J10.18
/colmix/COL2: H7.10, J10.17
/colmix/COL3: H7.13, J10.16
/colmix/COL4: H9.3, J10.14
/colmix/COL5: H9.6, J10.13
/colmix/COL6: H9.10, J10.12
/colmix/COL7: H9.13, J10.11
/colmix/COL8: H8.3, J10.93
/colmix/COL9: H8.6, J10.92
/colmix/COL10: H8.10, J10.91
/colmix/DS: F9.4, F9.13
/colmix/MCOL1: G8.8, G9.8, H7.4
/colmix/MCOL2: G8.7, G9.7, H7.7
/colmix/MCOL3: G8.6, G9.6, H7.9
/colmix/MCOL4: G8.5, G9.5, H7.12
/colmix/MCOL5: G8.4, G9.4, H9.4
/colmix/MCOL6: G8.3, G9.3, H9.7
/colmix/MCOL7: G8.2, G9.2, H9.9
/colmix/MCOL8: G8.1, G9.1, H9.12
/colmix/MCOL9: G8.23, G9.23, H8.4
/colmix/MCOL10: G8.22, G9.22, H8.7
/colmix/MCOL11: G8.19, G9.19, H8.9
/colmix/MCO~OE: G8.20, G9.20, H8.12
/colmix/RGB0: E8.3, G9.9, H6.18
/colmix/RGB1: E8.4, G9.10, H6.17
/colmix/RGB2: E8.7, G9.11, H6.16
/colmix/RGB3: E8.8, G9.13, H6.15
/colmix/RGB4: E8.13, G9.14, H6.14
/colmix/RGB5: E8.14, G9.15, H6.13
/colmix/RGB6: E8.17, G9.16, H6.12
/colmix/RGB7: E8.18, G9.17, H6.11
/colmix/RGB8: E7.3, G8.9, H5.18
/colmix/RGB9: E7.4, G8.10, H5.17
/colmix/RGB10: E7.7, G8.11, H5.16
/colmix/RGB11: E7.8, G8.13, H5.15
/colmix/RGB12: E7.13, G8.14, H5.14
/colmix/RGB13: E7.14, G8.15, H5.13
/colmix/RGB14: E7.17, G8.16, H5.12
/colmix/RGB15: G8.17, H5.11
/colmix/SHAD: F3.13, F12.8
/colmix/rgb/B11: D8.3, E7.9
/colmix/rgb/B12: D7.3, E7.12
/colmix/rgb/B13: D7.9, E7.15
/colmix/rgb/B14: D7.5, E7.16
/colmix/rgb/G5: D8.13, E8.15
/colmix/rgb/G6: D8.9, E8.16
/colmix/rgb/G7: C7.1, E8.19
/colmix/rgb/G8: D8.11, E7.2
/colmix/rgb/G9: C7.3, E7.5
/colmix/rgb/R0: C8.11, E8.2
/colmix/rgb/R1: C8.5, E8.5
/colmix/rgb/R2: D8.5, E8.6
/colmix/rgb/R3: C8.9, E8.9
/colmix/rgb/R4: C7.5, E8.12
/colmix/rgb/~SHD: C7.9, D7.11, D7.13, E7.19
/objects/CLKOBJ': J3.66, K10.11, K12.11, L1.11, L4.11, L6.11, L8.11, L10.11, L12.11
/objects/EA0: H2.11, J1.2, J3.113
/objects/EA1: H1.18, J1.10, J3.112
/objects/EA2: H1.17, J1.9, J3.110
/objects/EA3: H1.16, J1.8, J3.109
/objects/EA4: H2.9, J1.23, J3.108
/objects/EN0: H1.15, J1.7, J3.105
/objects/EN1: H1.14, J1.6, J3.104
/objects/EN2: H1.13, J1.5, J3.103
/objects/EN3: H1.12, J1.4, J3.102
/objects/EN4: H1.11, J1.3, J3.100
/objects/EN5: H2.3, J1.25, J3.99
/objects/EN6: H2.5, J1.24, J3.98
/objects/EN7: H2.7, J1.21, J3.97
/objects/G2D0: J3.32, J7.119
/objects/G2D1: J3.33, J7.118
/objects/G2D2: J3.34, J7.117
/objects/G2D3: J3.35, J7.116
/objects/G2D4: J3.36, J7.115
/objects/G2D5: J3.37, J7.114
/objects/G2D6: J3.38, J7.113
/objects/G2D7: J3.39, J7.112
/objects/G2D8: J3.40, J7.110
/objects/G2D9: J3.42, J7.109
/objects/G2D10: J3.43, J7.108
/objects/G2D11: J3.44, J7.107
/objects/G2D12: J3.45, J7.105
/objects/G2D13: J3.47, J7.104
/objects/G2D14: J3.48, J7.103
/objects/G2D15: J3.49, J7.102
/objects/G2D16: J3.50, J7.100
/objects/G2D17: J3.52, J7.99
/objects/G2D18: J3.53, J7.98
/objects/G2D19: J3.54, J7.97
/objects/G2D20: J3.55, J7.96
/objects/G2D21: J3.56, J7.95
/objects/LUTD0: H4.18, J1.11, J3.30
/objects/LUTD1: H4.17, J1.12, J3.29
/objects/LUTD2: H4.16, J1.13, J3.28
/objects/LUTD3: H4.15, J1.15, J3.27
/objects/LUTD4: H4.14, J1.16, J3.26
/objects/LUTD5: H4.13, J1.17, J3.25
/objects/LUTD6: H4.12, J1.18, J3.24
/objects/LUTD7: H4.11, J1.19, J3.23
/objects/OBJROMD'0: J7.72, K10.2, L1.2, L6.2, L10.2
/objects/OBJROMD'1: J7.73, K10.5, L1.5, L6.5, L10.5
/objects/OBJROMD'2: J7.74, K10.6, L1.6, L6.6, L10.6
/objects/OBJROMD'3: J7.75, K10.9, L1.9, L6.9, L10.9
/objects/OBJROMD'4: J7.77, K10.12, L1.12, L6.12, L10.12
/objects/OBJROMD'5: J7.78, K10.15, L1.15, L6.15, L10.15
/objects/OBJROMD'6: J7.79, K10.16, L1.16, L6.16, L10.16
/objects/OBJROMD'7: J7.80, K10.19, L1.19, L6.19, L10.19
/objects/OBJROMD'8: J7.82, K12.2, L4.2, L8.2, L12.2
/objects/OBJROMD'9: J7.83, K12.5, L4.5, L8.5, L12.5
/objects/OBJROMD'10: J7.84, K12.6, L4.6, L8.6, L12.6
/objects/OBJROMD'11: J7.85, K12.9, L4.9, L8.9, L12.9
/objects/OBJROMD'12: J7.86, K12.12, L4.12, L8.12, L12.12
/objects/OBJROMD'13: J7.87, K12.15, L4.15, L8.15, L12.15
/objects/OBJROMD'14: J7.88, K12.16, L4.16, L8.16, L12.16
/objects/OBJROMD'15: J7.89, K12.19, L4.19, L8.19, L12.19
/objects/OBJ~REG: J3.2, J7.2
/objects/~CPU: H1.19, H2.1, H2.15, H3.1, J3.116
/objects/~RD: H2.13, J1.22, J3.114
/objects/~SET0: J3.65, J7.90, L1.1, L4.1
/objects/~SET1: J3.64, J7.92, L6.1, L8.1
/objects/~SET2: J3.63, J7.93, L10.1, L12.1
/objects/~SET3: J3.62, J7.94, K10.1, K12.1
/scroll/COL5: G13.43, J13.109
/scroll/COL6: G13.46, J13.108
/scroll/COL7: G13.22, J13.107
/scroll/GFXROMA0: G13.35, H16.9, H18.9
/scroll/GFXROMA1: G13.34, H16.8, H18.8
/scroll/GFXROMA2: G13.33, H16.7, H18.7
/scroll/GFXROMA3: G13.32, H16.6, H18.6
/scroll/GFXROMA4: G13.30, H16.5, H18.5
/scroll/GFXROMA5: G13.29, H16.4, H18.4
/scroll/GFXROMA6: G13.28, H16.3, H18.3
/scroll/GFXROMA7: G13.27, H16.2, H18.2
/scroll/GFXROMA8: G13.26, H16.40, H18.40
/scroll/GFXROMA9: G13.25, H16.39, H18.39
/scroll/GFXROMA10: G13.24, H16.38, H18.38
/scroll/GFXROMA11: G13.37, H16.37, H18.37
/scroll/GFXROMA12: G13.38, H16.36, H18.36
/scroll/GFXROMA13: G13.39, H16.35, H18.35
/scroll/GFXROMA14: G13.40, H16.34, H18.34
/scroll/GFXROMA15: G13.41, H16.33, H18.33
/scroll/GFXROMA16: G13.42, H16.32, H18.32
/scroll/GFXROMA17: G13.23, H16.1, H18.1
/scroll/GFXROMD0: H18.13, J13.29
/scroll/GFXROMD1: H18.15, J13.28
/scroll/GFXROMD2: H18.17, J13.27
/scroll/GFXROMD3: H18.19, J13.26
/scroll/GFXROMD4: H18.22, J13.25
/scroll/GFXROMD5: H18.24, J13.24
/scroll/GFXROMD6: H18.26, J13.23
/scroll/GFXROMD7: H18.28, J13.22
/scroll/GFXROMD8: H18.14, J13.21
/scroll/GFXROMD9: H18.16, J13.20
/scroll/GFXROMD10: H18.18, J13.19
/scroll/GFXROMD11: H18.20, J13.18
/scroll/GFXROMD12: H18.23, J13.17
/scroll/GFXROMD13: H18.25, J13.16
/scroll/GFXROMD14: H18.27, J13.13
/scroll/GFXROMD15: H18.29, J13.12
/scroll/GFXROMD16: H16.13, J13.11
/scroll/GFXROMD17: H16.15, J13.10
/scroll/GFXROMD18: H16.17, J13.9
/scroll/GFXROMD19: H16.19, J13.8
/scroll/GFXROMD20: H16.22, J13.7
/scroll/GFXROMD21: H16.24, J13.6
/scroll/GFXROMD22: H16.26, J13.5
/scroll/GFXROMD23: H16.28, J13.4
/scroll/GFXROMD24: H16.14, J13.3
/scroll/GFXROMD25: H16.16, J13.2
/scroll/GFXROMD26: H16.18, J13.120
/scroll/GFXROMD27: H16.20, J13.119
/scroll/GFXROMD28: H16.23, J13.118
/scroll/GFXROMD29: H16.25, J13.117
/scroll/GFXROMD30: H16.27, J13.116
/scroll/GFXROMD31: H16.29, J13.115
/scroll/PREPE: E18.4, G13.90
/scroll/SCRAMA0: F16.10, G13.2, G16.10
/scroll/SCRAMA1: F16.9, G13.120, G16.9
/scroll/SCRAMA2: F16.8, G13.119, G16.8
/scroll/SCRAMA3: F16.7, G13.118, G16.7
/scroll/SCRAMA4: F16.6, G13.117, G16.6
/scroll/SCRAMA5: F16.5, G13.70, G16.5
/scroll/SCRAMA6: F16.4, G13.71, G16.4
/scroll/SCRAMA7: F16.3, G13.72, G16.3
/scroll/SCRAMA8: F16.25, G13.73, G16.25
/scroll/SCRAMA9: F16.24, G13.76, G16.24
/scroll/SCRAMA10: F16.21, G13.77, G16.21
/scroll/SCRAMA11: F16.23, G13.78, G16.23
/scroll/SCRAMA12: F16.2, G13.79, G16.2
/scroll/SCR~CLK: G13.65, J13.90
/scroll/VD0: G13.20, G16.11
/scroll/VD1: G13.19, G16.12
/scroll/VD2: G13.18, G16.13
/scroll/VD3: G13.17, G16.15
/scroll/VD4: G13.16, G16.16
/scroll/VD5: G13.13, G16.17
/scroll/VD6: G13.12, G16.18
/scroll/VD7: G13.11, G16.19
/scroll/VD8: F16.11, G13.10
/scroll/VD9: F16.12, G13.9
/scroll/VD10: F16.13, G13.8
/scroll/VD11: F16.15, G13.7
/scroll/VD12: F16.16, G13.6
/scroll/VD13: F16.17, G13.5
/scroll/VD14: F16.18, G13.4
/scroll/VD15: F16.19, G13.3
/scroll/VRAM~CS: G13.54, G13.84, J13.97
/scroll/ZA1H: G13.50, J13.101
/scroll/ZA2H: G13.51, J13.100
/scroll/ZA4H: G13.52, J13.99
/scroll/ZB1H: G13.47, J13.106
/scroll/ZB2H: G13.48, J13.103
/scroll/ZB4H: G13.49, J13.102
/scroll/~BE: G13.53, J13.98
/scroll/~CSYNC: E18.14, J13.76
/scroll/~ROE1: F16.22, G13.95
/scroll/~ROE2: G13.96, G16.22
/scroll/~RWE1: F16.27, G13.107
/scroll/~RWE2: G13.108, G16.27
/~HBLANK: E12.2, J13.70
/~HSYNC: J3.8, J7.8, J13.73
/~RESET: E12.9, E18.12, G13.98
/~SYSRES: E10.2, G13.55, J3.3, J7.3, J13.92
/~VBLANK: E12.1, J3.119, J13.69
A0: G13.66, G13.67, H1.2, H7.5, J3.4, J3.7, J7.4, J7.7, J10.84, J13.88, J13.89
A1: G13.68, H1.4, H7.11, J3.6, J7.6, J10.83
A2: G13.69, H1.5, H7.14, J10.82
A3: G13.116, H1.6, H9.2
A4: G13.115, H1.7, H9.5
A5: G13.114, H1.8, H9.11
A6: G13.113, H1.9, H9.14
A7: G13.112, H2.2, H8.2
A8: G13.111, H2.4, H8.5
A9: G13.110, H2.6, H8.11
A10: G13.109, H2.10
A11: G13.80, H2.12
unnamed: BB8.6, D7.2
unnamed: BB8.5, D8.4
unnamed: BB8.4, D7.4
unnamed: BB8.3, D7.8
unnamed: BB8.2, D7.6
unnamed: BG8.7, C8.2
unnamed: BG8.6, D8.12
unnamed: BG8.5, D8.8
unnamed: BG8.4, C7.2
unnamed: BG8.3, D8.10
unnamed: BG8.2, C7.4
unnamed: BR8.7, C8.4
unnamed: BR8.6, C8.10
unnamed: BR8.5, C8.6
unnamed: BR8.4, D8.6
unnamed: BR8.3, C8.8
unnamed: BR8.2, C7.6
unnamed: E7.18, F3.12
unnamed: C8.1, C8.3, D7.1, E12.11
unnamed: F9.9, U2.10
unnamed: F9.8, F9.12
unnamed: F9.5, F10.3
unnamed: F13.3, H3.2
unnamed: E10.3, F13.4
unnamed: F9.6, G8.21
unnamed: F9.11, G9.21
unnamed: J1.27, U1.3
unnamed: F12.10, J10.87
unnamed: F12.9, J10.86
VCC: BB8.1, BG8.1, BR8.1, E7.1, E8.1, E12.14, E18.16, F13.1, F16.26, F16.28, G8.24, G9.24, G13.14, G13.44, G13.74, G13.104, G16.26, G16.28, H1.1, H2.16, H16.21, H18.21, J1.26, J1.28, J3.16, J3.46, J3.60, J3.76, J3.106, J3.120, J7.16, J7.46, J7.60, J7.70, J7.76, J7.106, J7.120, J10.1, J10.2, J10.3, J10.28, J10.39, J10.42, J10.43, J10.44, J10.45, J10.46, J10.53, J10.78, J10.97, J10.98, J10.99, J10.100, J13.14, J13.44, J13.74, J13.104, L16.22, L16.31, N3.22, N3.31, N8.22, N8.31, N12.22, N12.31
VSS: BB8.9, BG8.9, BR8.9, E12.7, E18.1, E18.8, E18.15, F13.2, F16.14, F16.20, G8.12, G8.18, G9.12, G9.18, G13.1, G13.15, G13.21, G13.31, G13.45, G13.61, G13.75, G13.91, G13.105, G16.14, G16.20, H2.8, H7.15, H8.13, H8.15, H9.15, H16.10, H16.11, H16.12, H16.30, H16.31, H18.10, H18.11, H18.12, H18.30, H18.31, J1.14, J1.20, J3.5, J3.91, J3.101, J3.111, J3.117, J3.118, J7.1, J7.5, J7.11, J7.21, J7.31, J7.41, J7.51, J7.61, J7.62, J7.63, J7.64, J7.65, J7.66, J7.67, J7.68, J7.69, J7.71, J7.81, J7.91, J7.101, J7.111, J10.4, J10.5, J10.6, J10.7, J10.8, J10.9, J10.10, J10.15, J10.20, J10.21, J10.22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
